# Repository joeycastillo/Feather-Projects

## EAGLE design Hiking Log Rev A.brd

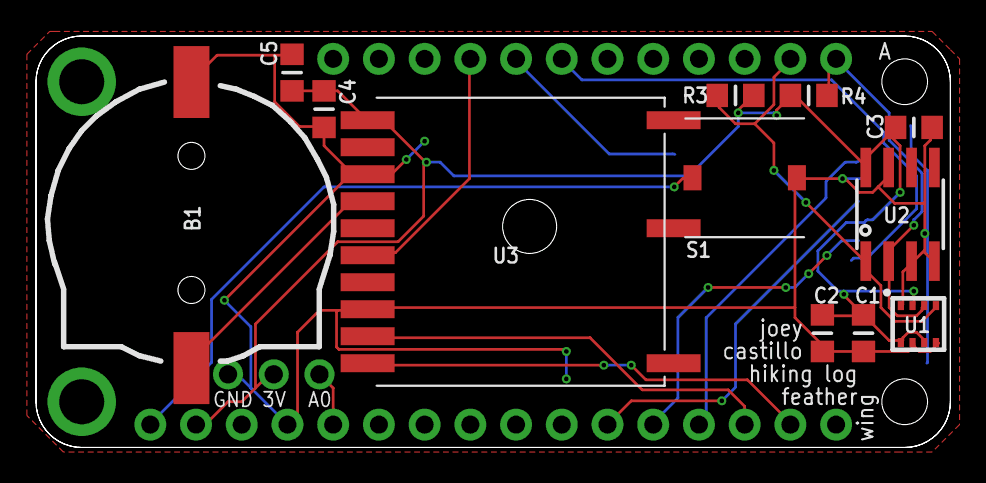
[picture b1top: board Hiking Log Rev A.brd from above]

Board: 2 copper layers, 50.8 x 22.9 mm, 15 parts (1 on the bottom side), 15 nets.

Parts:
B1: CR1220; CR1220-2
C1, C2, C3: 0.1uF; _0805MP
C4: 0.01uF; _0805MP
C5: 1uF; _0805MP
JP1: 1X03-CLEANBIG
MS1: FEATHERWING
R3, R4: 10K; _0805MP
S1: MINISOFTTOUCHBUTTON
U1: BME280; BME280_LGA
U2: ADT7410; SOIC8_150MIL
U3: FGPMMOPA6C
X1: MICROSD

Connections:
1PPS: MS1.25, U3.P$6
3.3V: C1.1, C2.1, C3.1, C4.1, C5.1, JP1.2, MS1.2, R3.2, R4.2, U1.P$2, U1.P$6, U1.P$8, U2.8, U3.P$1, X1.4
CD: MS1.24, X1.CD1
GND: B1.-, C1.2, C2.2, C3.2, C4.2, C5.2, JP1.1, MS1.4, S1.P$1, U1.P$1, U1.P$5, U1.P$7, U2.3, U2.4, U2.7, U3.P$3, U3.P$8, X1.6, X1.MT1, X1.MT2
GPIOA0: JP1.3, MS1.5
GPSRX: MS1.15, U3.P$10
GPSTX: MS1.14, U3.P$9
MISO: MS1.13, X1.7
MOSI: MS1.12, X1.3
RST: MS1.1, S1.P$2
SCK: MS1.11, X1.5
SCL: MS1.18, R3.1, U1.P$4, U2.1
SDA: MS1.17, R4.1, U1.P$3, U2.2
SDCS: MS1.23, X1.2
VBACKUP: B1.+, U3.P$4

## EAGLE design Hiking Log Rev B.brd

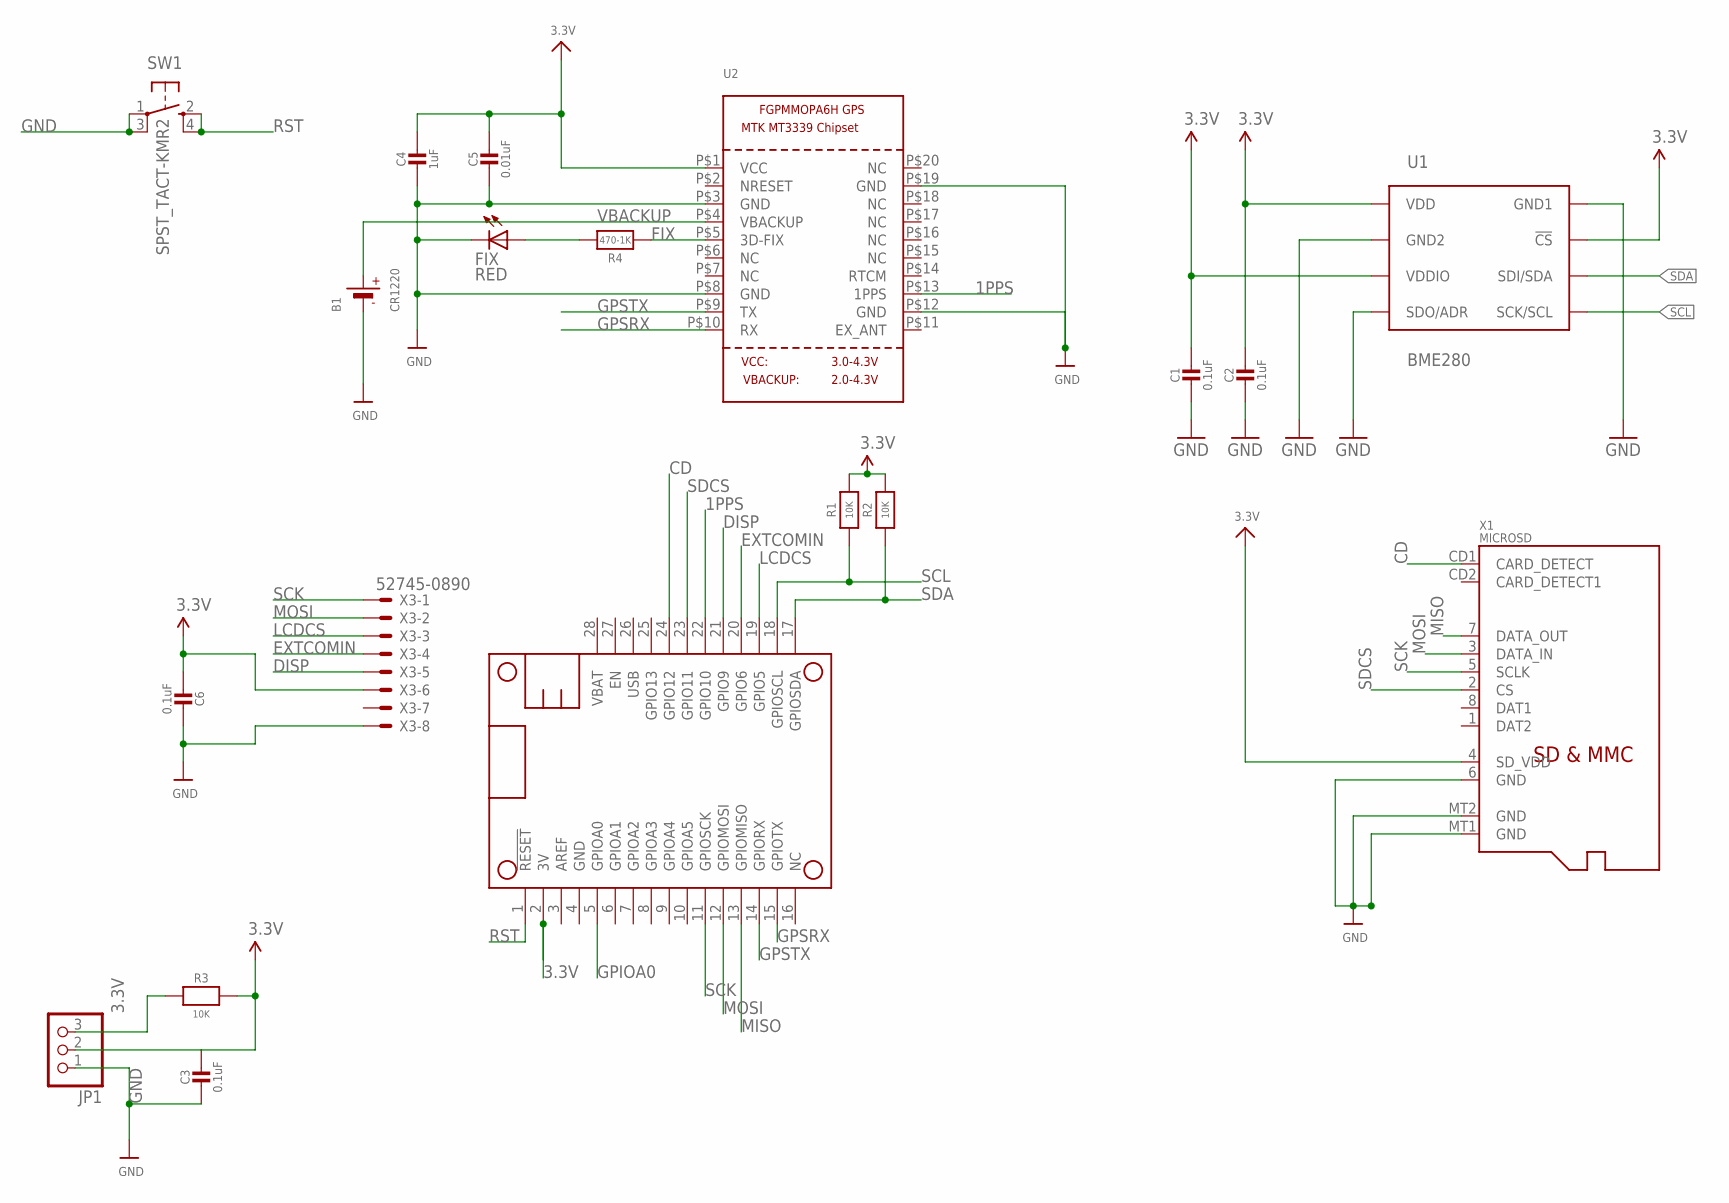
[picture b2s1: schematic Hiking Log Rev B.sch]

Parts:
B1: CR1220; CR1220-2
C1, C2, C3, C6: 0.1uF; _0805MP
C4: 1uF; _0805MP
C5: 0.01uF; _0805MP
FIX: RED; CHIP-LED0805
JP1: PINHD-1X3CB; 1X03-CLEANBIG
MS1: FEATHERWING
R1, R2, R3: 10K; _0805MP
R4: 470-1K; _0805MP
SW1: SPST_TACT-KMR2; KMR2
U1: BME280; BME280_LGA
U2: GPS_FGPMMOPA6H; FGPMMOPA6H
X1: MICROSD
X3: 52745-0890

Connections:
1PPS: MS1.22 (GPIO10), U2.P$13 (1PPS)
3.3V: C1.1, C2.1, C3.1, C4.1, C5.1, C6.2, JP1.2, MS1.2 (3V), R1.2, R2.2, R3.2, U1.P$2 (!CS), U1.P$6 (VDDIO), U1.P$8 (VDD), U2.P$1 (VCC), X1.4 (SD_VDD), X3.6
CD: MS1.24 (GPIO12), X1.CD1 (CARD_DETECT)
DISP: MS1.21 (GPIO9), X3.5
EXTCOMIN: MS1.20 (GPIO6), X3.4
FIX: R4.1, U2.P$5 (3D-FIX)
GND: B1.-, C1.2, C2.2, C3.2, C4.2, C5.2, C6.1, FIX.C, JP1.1, MS1.4 (GND), SW1.1, SW1.3 (P1), U1.P$1 (GND1), U1.P$5 (SDO/ADR), U1.P$7 (GND2), U2.P$3 (GND), U2.P$8 (GND), U2.P$12 (GND), U2.P$19 (GND), X1.6 (GND), X1.MT1 (GND), X1.MT2 (GND), X3.8
GPIOA0: JP1.3, MS1.5 (GPIOA0), R3.1
GPSRX: MS1.15 (GPIOTX), U2.P$10 (RX)
GPSTX: MS1.14 (GPIORX), U2.P$9 (TX)
LCDCS: MS1.19 (GPIO5), X3.3
MISO: MS1.13 (GPIOMISO), X1.7 (DATA_OUT)
MOSI: MS1.12 (GPIOMOSI), X1.3 (DATA_IN), X3.2
unnamed: FIX.A, R4.2
RST: MS1.1 (!RESET), SW1.2 (S), SW1.4 (S1)
SCK: MS1.11 (GPIOSCK), X1.5 (SCLK), X3.1
SCL: MS1.18 (GPIOSCL), R1.1, U1.P$4 (SCK/SCL)
SDA: MS1.17 (GPIOSDA), R2.1, U1.P$3 (SDI/SDA)
SDCS: MS1.23 (GPIO11), X1.2 (CS)
VBACKUP: B1.+, U2.P$4 (VBACKUP)

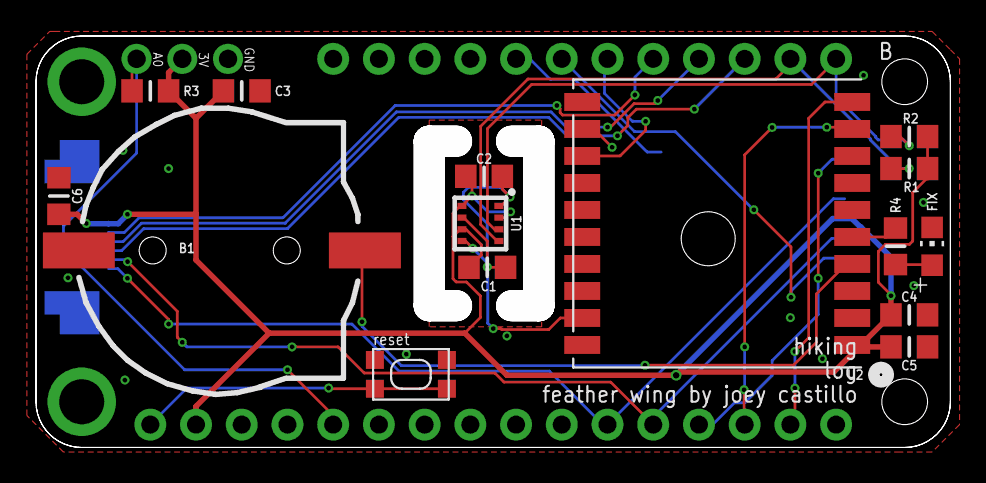
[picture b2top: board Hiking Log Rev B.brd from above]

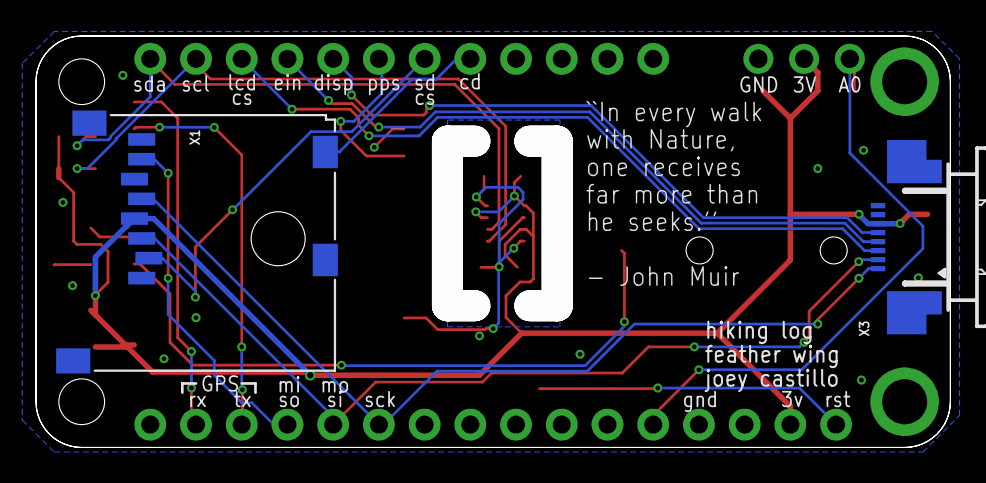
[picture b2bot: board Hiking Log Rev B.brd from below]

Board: 2 copper layers, 50.8 x 22.9 mm, 19 parts (2 on the bottom side), 20 nets.

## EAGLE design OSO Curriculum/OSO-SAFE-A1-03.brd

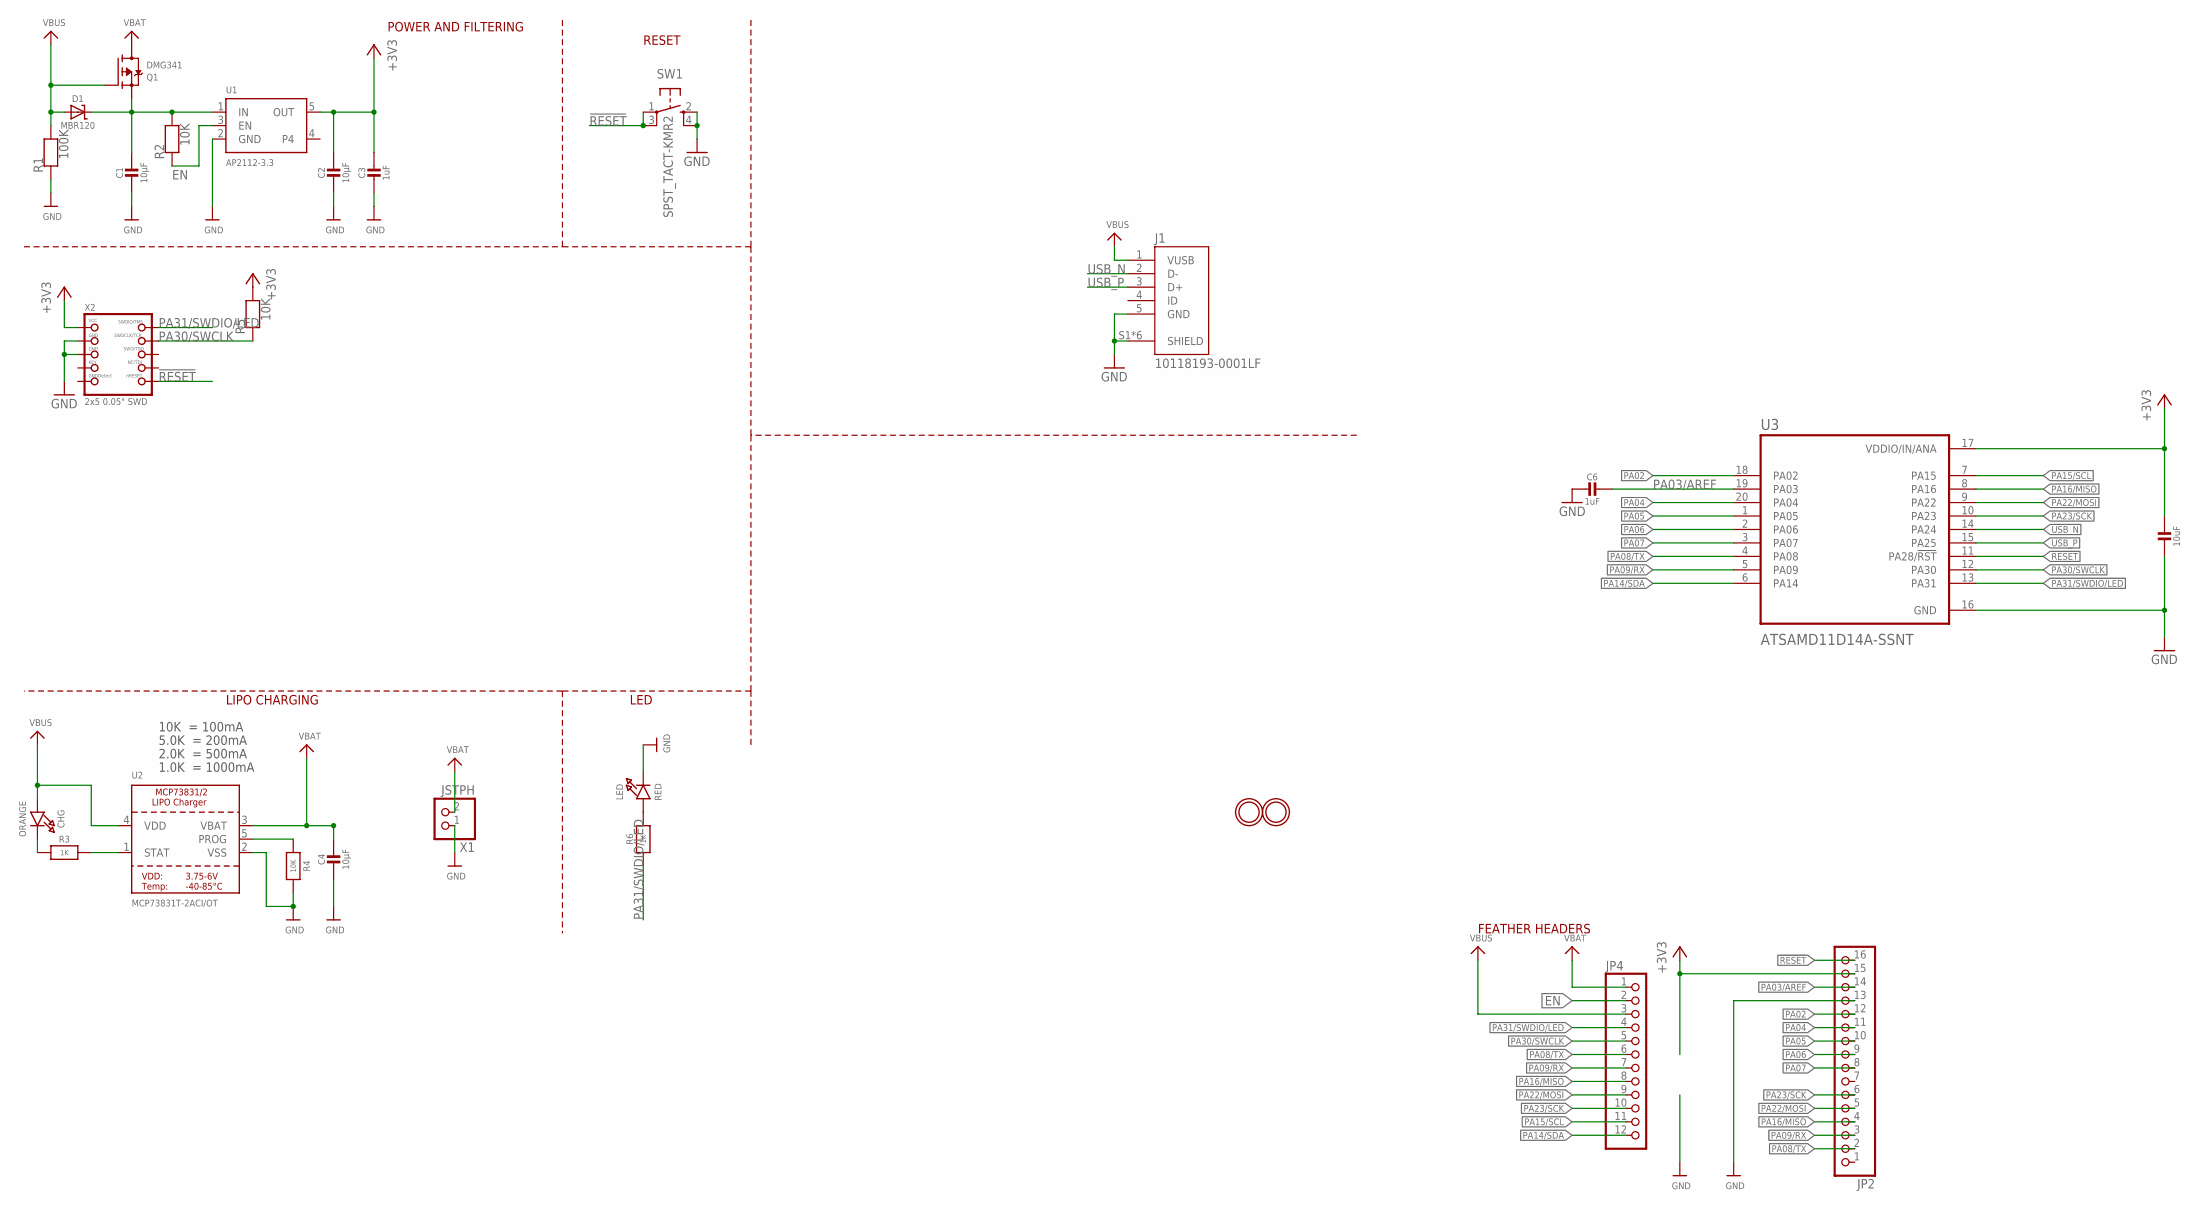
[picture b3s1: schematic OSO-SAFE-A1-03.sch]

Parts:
C1, C2, C4: 10µF; 0805-NO
C3, C6: 1uF; 0805-NO
C5: 10uF; 0805-NO
CHG: ORANGE; CHIPLED_0805_NOOUTLINE
D1: MBR120; SOD-123
J1: 10118193-0001LF; FCI_10118193-0001LF
JP2: HEADER-1X16_MIN; 1X16_ROUND_MIN
JP4: HEADER-1X12_MIN; 1X12_ROUND_MIN
LED: RED; CHIPLED_0805_NOOUTLINE
Q1: DMG341; SOT23-R
R1: 100K; 0805-NO
R2, R4, R5: 10K; 0805-NO
R3, R6: 1K; 0805-NO
SW1: SPST_TACT-KMR2; KMR2
U1: AP2112-3.3; SOT23-5
U2: MCP73831T-2ACI/OT; SOT23-5
U3: ATSAMD11D14A-SSNT; SOIC127P1030X265-20N
U$31, U$32: MOUNTINGHOLE2.5; MOUNTINGHOLE_2.5_PLATED
X1: JSTPH; JSTPH2
X2: 2x5 0.05" SWD; 2X05_1.27MM_BOX_POSTS

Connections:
!RESET: JP2.16, SW1.1, SW1.3 (P1), U3.11 (PA28/!RST), X2.10 (NRESET)
+3V3: C2.1, C3.1, C5.1, JP2.15, R5.2, U1.5 (OUT), U3.17 (VDDIO/IN/ANA), X2.1 (VCC)
CHG: CHG.C, R3.1
EN: JP4.2, R2.1, U1.3 (EN)
GND: C1.2, C2.2, C3.2, C4.2, C5.2, C6.2, J1.5 (GND), J1.S1 (SHIELD), J1.S2 (SHIELD), J1.S3 (SHIELD), J1.S4 (SHIELD), J1.S5 (SHIELD), J1.S6 (SHIELD), JP2.13, LED.C, R1.1, R4.2, SW1.2 (S), SW1.4 (S1), U1.2 (GND), U2.2 (VSS), U3.16 (GND), X1.1, X2.3 (GND), X2.5 (GND)
unnamed: LED.A, R6.2
PA02: JP2.12, U3.18 (PA02)
PA03/AREF: C6.1, JP2.14, U3.19 (PA03)
PA04: JP2.11, U3.20 (PA04)
PA05: JP2.10, U3.1 (PA05)
PA06: JP2.9, U3.2 (PA06)
PA07: JP2.8, U3.3 (PA07)
PA08/TX: JP2.2, JP4.6, U3.4 (PA08)
PA09/RX: JP2.3, JP4.7, U3.5 (PA09)
PA14/SDA: JP4.12, U3.6 (PA14)
PA15/SCL: JP4.11, U3.7 (PA15)
PA16/MISO: JP2.4, JP4.8, U3.8 (PA16)
PA22/MOSI: JP2.5, JP4.9, U3.9 (PA22)
PA23/SCK: JP2.6, JP4.10, U3.10 (PA23)
PA30/SWCLK: JP4.5, R5.1, U3.12 (PA30), X2.4 (SWDCLK)
PA31/SWDIO/LED: JP4.4, R6.1, U3.13 (PA31), X2.2 (SWDIO)
PROG: R4.1, U2.5 (PROG)
STAT: R3.2, U2.1 (STAT)
USB_N: J1.2 (D-), U3.14 (PA24)
USB_P: J1.3 (D+), U3.15 (PA25)
VBAT: C4.1, JP4.1, Q1.3 (D), U2.3 (VBAT), X1.2
VBUS: CHG.A, D1.A, J1.1 (VUSB), JP4.3, Q1.1 (G), R1.2, U2.4 (VDD)
VHI: C1.1, D1.C, Q1.2 (S), R2.2, U1.1 (IN)

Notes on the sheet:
LIPO CHARGING
LED
RESET
POWER AND FILTERING
10K = 100mA
5.0K = 200mA
2.0K = 500mA
1.0K = 1000mA
FEATHER HEADERS

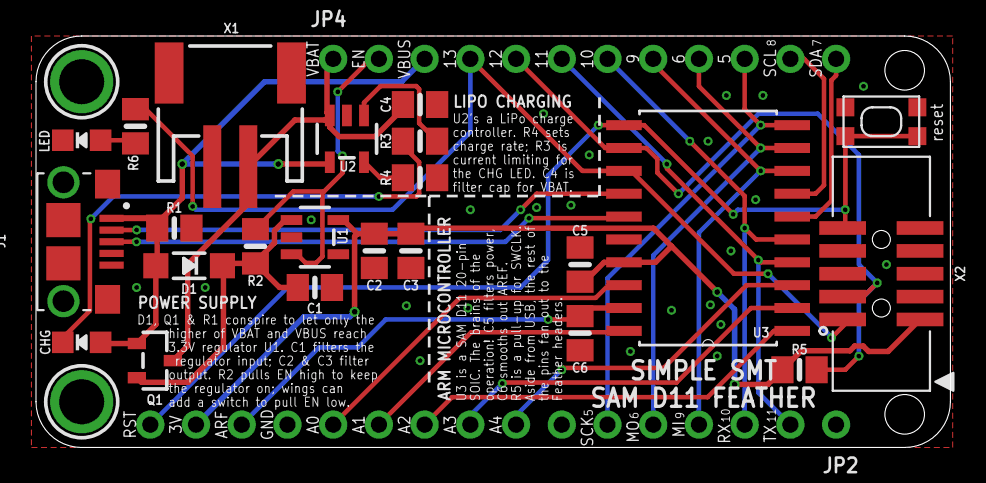
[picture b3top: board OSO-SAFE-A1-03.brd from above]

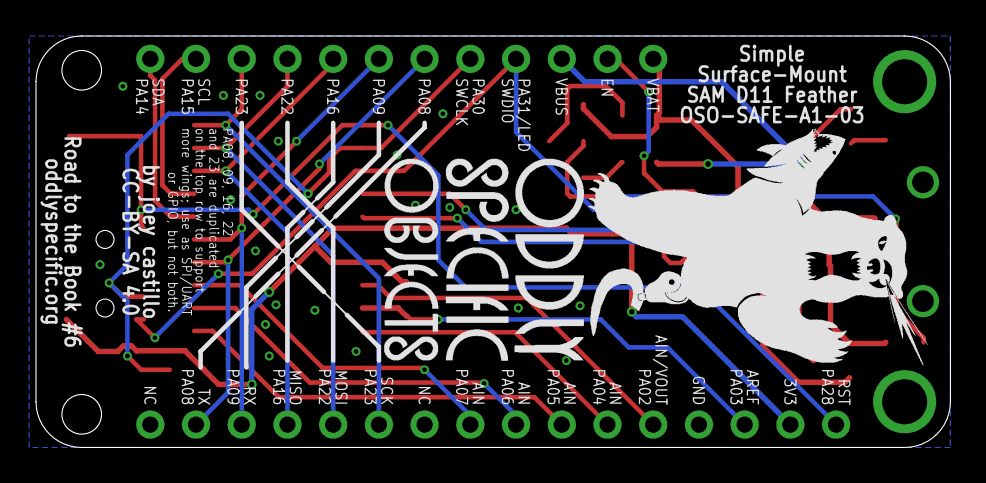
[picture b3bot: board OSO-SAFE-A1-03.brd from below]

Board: 2 copper layers, 50.8 x 22.9 mm, 29 parts (2 on the bottom side), 28 nets.

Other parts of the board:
U$6: OSO_BEAR_525X750MIL_1000DPI
U$7: OSO_WORDMARK_THREELINE_450MIL_1000DPI

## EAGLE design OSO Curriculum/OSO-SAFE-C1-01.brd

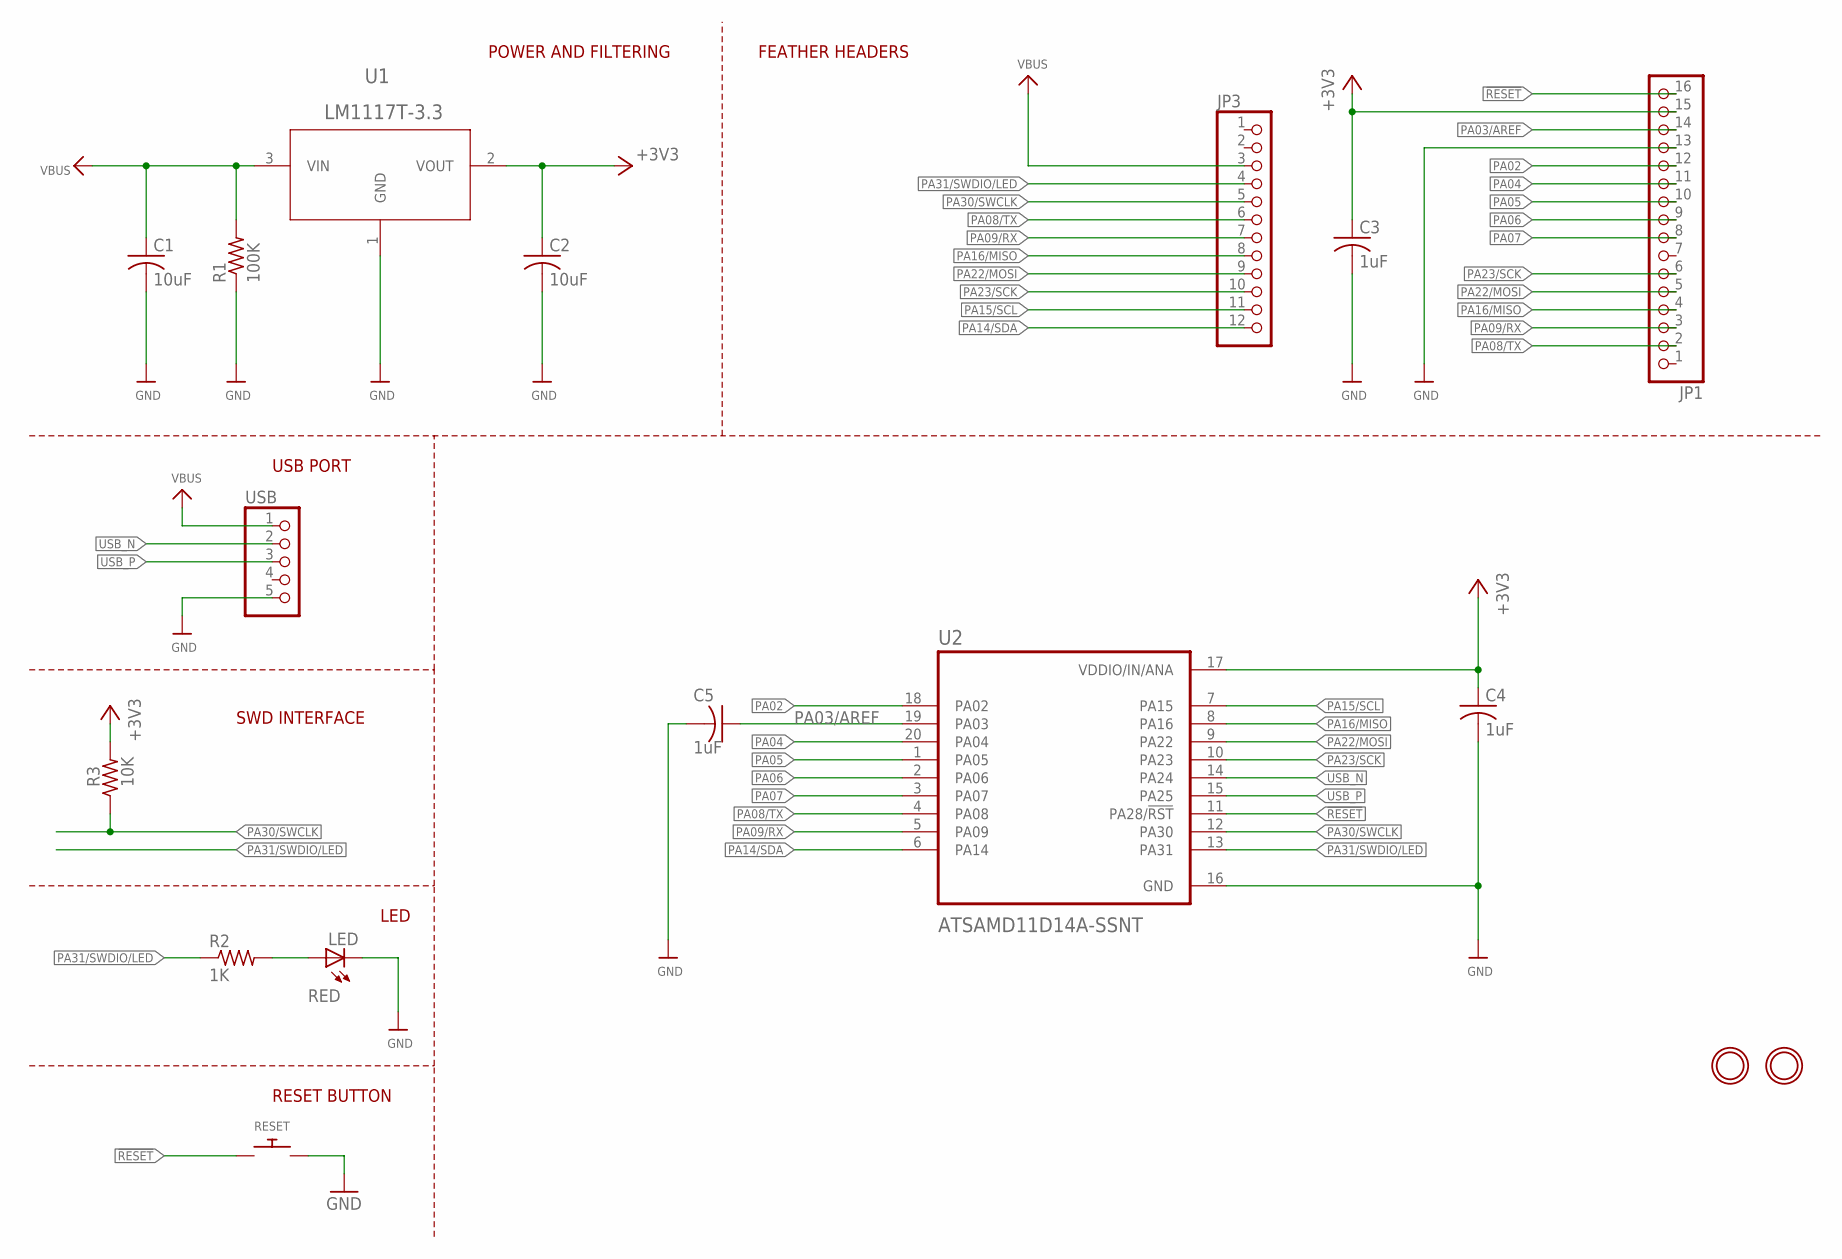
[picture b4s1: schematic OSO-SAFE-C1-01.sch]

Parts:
C1, C2: 10uF; C050-025X075
C3, C4, C5: 1uF; C025-025X050
JP1: HEADER-1X16_MIN; 1X16_ROUND_MIN
JP3: HEADER-1X12_MIN; 1X12_ROUND_MIN
LED: RED; LED3MM
R1: 100K; 0207/9
R2: 1K; 0207/9
R3: 10K; 0207/9
RESET: SWITCH_PUSHBUTTONEVQ-PE; TACT_PANA-EVQ
U1: LM1117T-3.3; T03B
U2: ATSAMD11D14A-SSNT; SOIC127P1030X265-20N
U$10, U$32: MOUNTINGHOLE2.5; MOUNTINGHOLE_2.5_PLATED
USB: PINHD-1X5; 1X05

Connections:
!RESET: JP1.16, RESET.P$1, U2.11 (PA28/!RST)
+3V3: C2.1, C3.1, C4.1, JP1.15, R3.2, U1.2 (VOUT), U2.17 (VDDIO/IN/ANA)
GND: C1.2, C2.2, C3.2, C4.2, C5.2, JP1.13, LED.K (C), R1.1, RESET.P$2, U1.1 (GND), U2.16 (GND), USB.5
unnamed: LED.A, R2.2
PA02: JP1.12, U2.18 (PA02)
PA03/AREF: C5.1, JP1.14, U2.19 (PA03)
PA04: JP1.11, U2.20 (PA04)
PA05: JP1.10, U2.1 (PA05)
PA06: JP1.9, U2.2 (PA06)
PA07: JP1.8, U2.3 (PA07)
PA08/TX: JP1.2, JP3.6, U2.4 (PA08)
PA09/RX: JP1.3, JP3.7, U2.5 (PA09)
PA14/SDA: JP3.12, U2.6 (PA14)
PA15/SCL: JP3.11, U2.7 (PA15)
PA16/MISO: JP1.4, JP3.8, U2.8 (PA16)
PA22/MOSI: JP1.5, JP3.9, U2.9 (PA22)
PA23/SCK: JP1.6, JP3.10, U2.10 (PA23)
PA30/SWCLK: JP3.5, R3.1, U2.12 (PA30)
PA31/SWDIO/LED: JP3.4, R2.1, U2.13 (PA31)
USB_N: U2.14 (PA24), USB.2
USB_P: U2.15 (PA25), USB.3
VBUS: C1.1, JP3.3, R1.2, U1.3 (VIN), USB.1

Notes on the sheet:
RESET BUTTON
POWER AND FILTERING
FEATHER HEADERS
LED
SWD INTERFACE
USB PORT

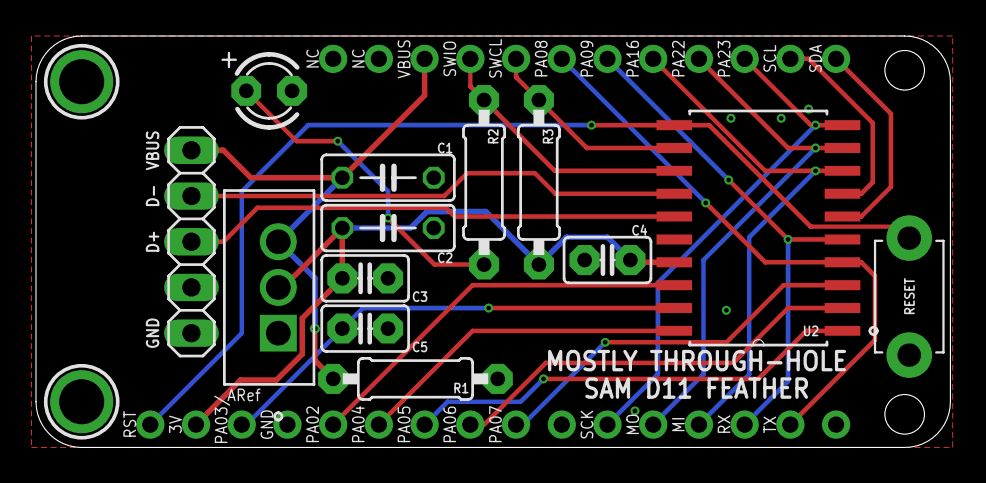
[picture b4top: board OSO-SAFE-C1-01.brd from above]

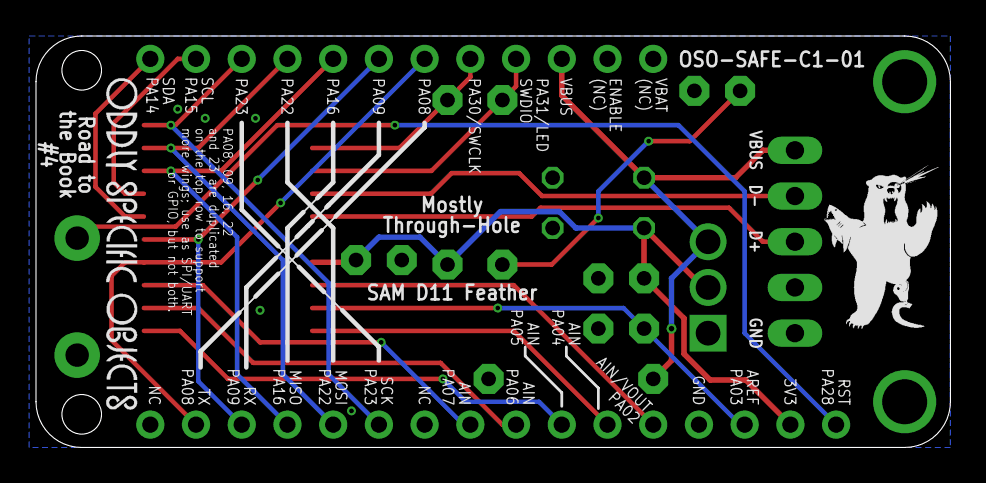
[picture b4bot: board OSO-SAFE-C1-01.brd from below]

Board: 2 copper layers, 50.8 x 22.9 mm, 19 parts (2 on the bottom side), 22 nets.

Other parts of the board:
U$8: OSO_WORDMARK_ONELINE_725MIL_1000DPI
U$9: OSO_BEAR_250X360MIL_1000DPI

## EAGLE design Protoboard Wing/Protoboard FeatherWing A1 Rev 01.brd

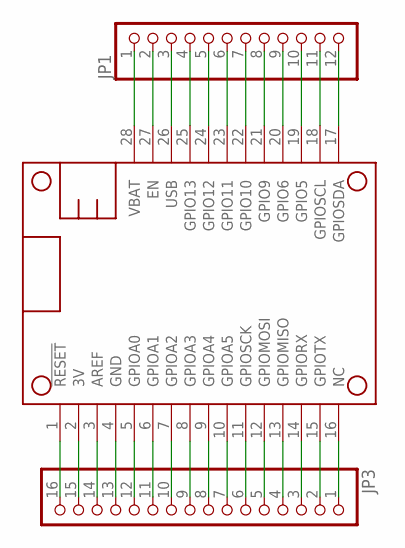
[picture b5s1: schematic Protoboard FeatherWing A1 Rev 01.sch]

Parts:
JP1: HEADER-1X1276MIL; 1X12_ROUND_76MIL
JP3: HEADER-1X16_76MIL; 1X16_ROUND_76MIL
MS1: FEATHERWING

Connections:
3V: JP3.15, MS1.2 (3V)
AREF: JP3.14, MS1.3 (AREF)
GND: JP3.13, MS1.4 (GND)
unnamed: JP1.2, MS1.27 (EN)
unnamed: JP3.1, MS1.16 (NC)
unnamed: JP1.4, MS1.25 (GPIO13)
unnamed: JP3.2, MS1.15 (GPIOTX)
unnamed: JP1.5, MS1.24 (GPIO12)
unnamed: JP3.3, MS1.14 (GPIORX)
unnamed: JP3.4, MS1.13 (GPIOMISO)
unnamed: JP3.5, MS1.12 (GPIOMOSI)
unnamed: JP3.6, MS1.11 (GPIOSCK)
unnamed: JP3.7, MS1.10 (GPIOA5)
unnamed: JP3.8, MS1.9 (GPIOA4)
unnamed: JP3.9, MS1.8 (GPIOA3)
unnamed: JP3.10, MS1.7 (GPIOA2)
unnamed: JP3.11, MS1.6 (GPIOA1)
unnamed: JP3.12, MS1.5 (GPIOA0)
unnamed: JP3.16, MS1.1 (!RESET)
unnamed: JP1.6, MS1.23 (GPIO11)
unnamed: JP1.7, MS1.22 (GPIO10)
unnamed: JP1.8, MS1.21 (GPIO9)
unnamed: JP1.9, MS1.20 (GPIO6)
unnamed: JP1.10, MS1.19 (GPIO5)
unnamed: JP1.11, MS1.18 (GPIOSCL)
unnamed: JP1.12, MS1.17 (GPIOSDA)
USB: JP1.3, MS1.26 (USB)
VBAT: JP1.1, MS1.28 (VBAT)

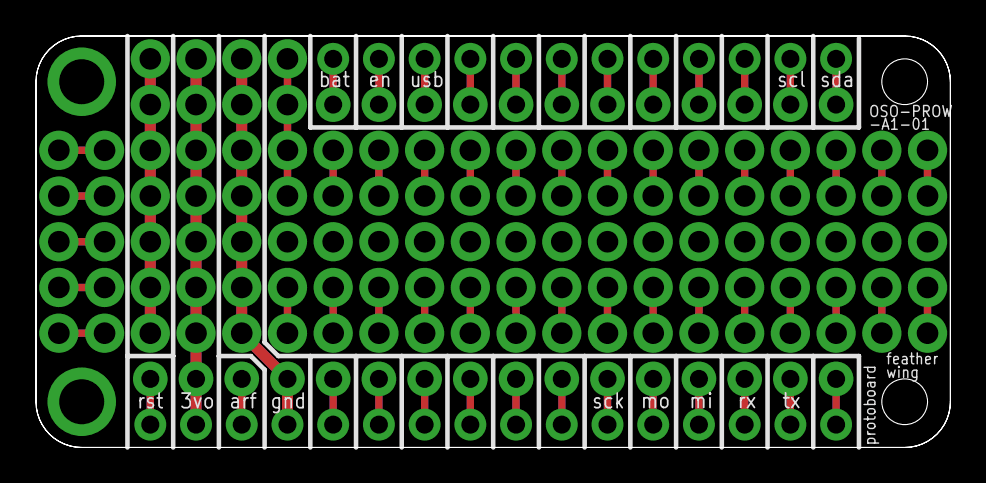
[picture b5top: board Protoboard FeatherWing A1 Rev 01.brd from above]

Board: 2 copper layers, 50.8 x 22.9 mm, 3 parts (0 on the bottom side), 28 nets.

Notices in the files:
OSO Curriculum/OSO-SAFE-A1-03.brd:
CC-BY-SA 4.0
parts and their libraries:
SparkFun-Aesthetics: Licensing: Creative Commons ShareAlike 4.0 International - https://creativecommons.org/licenses/by-sa/4.0
My Stuff: cc-by-sa 3.0
microbuilder: This work is placed in the public domain, and may be freely used for commercial and non-commercial work with the following conditions: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
